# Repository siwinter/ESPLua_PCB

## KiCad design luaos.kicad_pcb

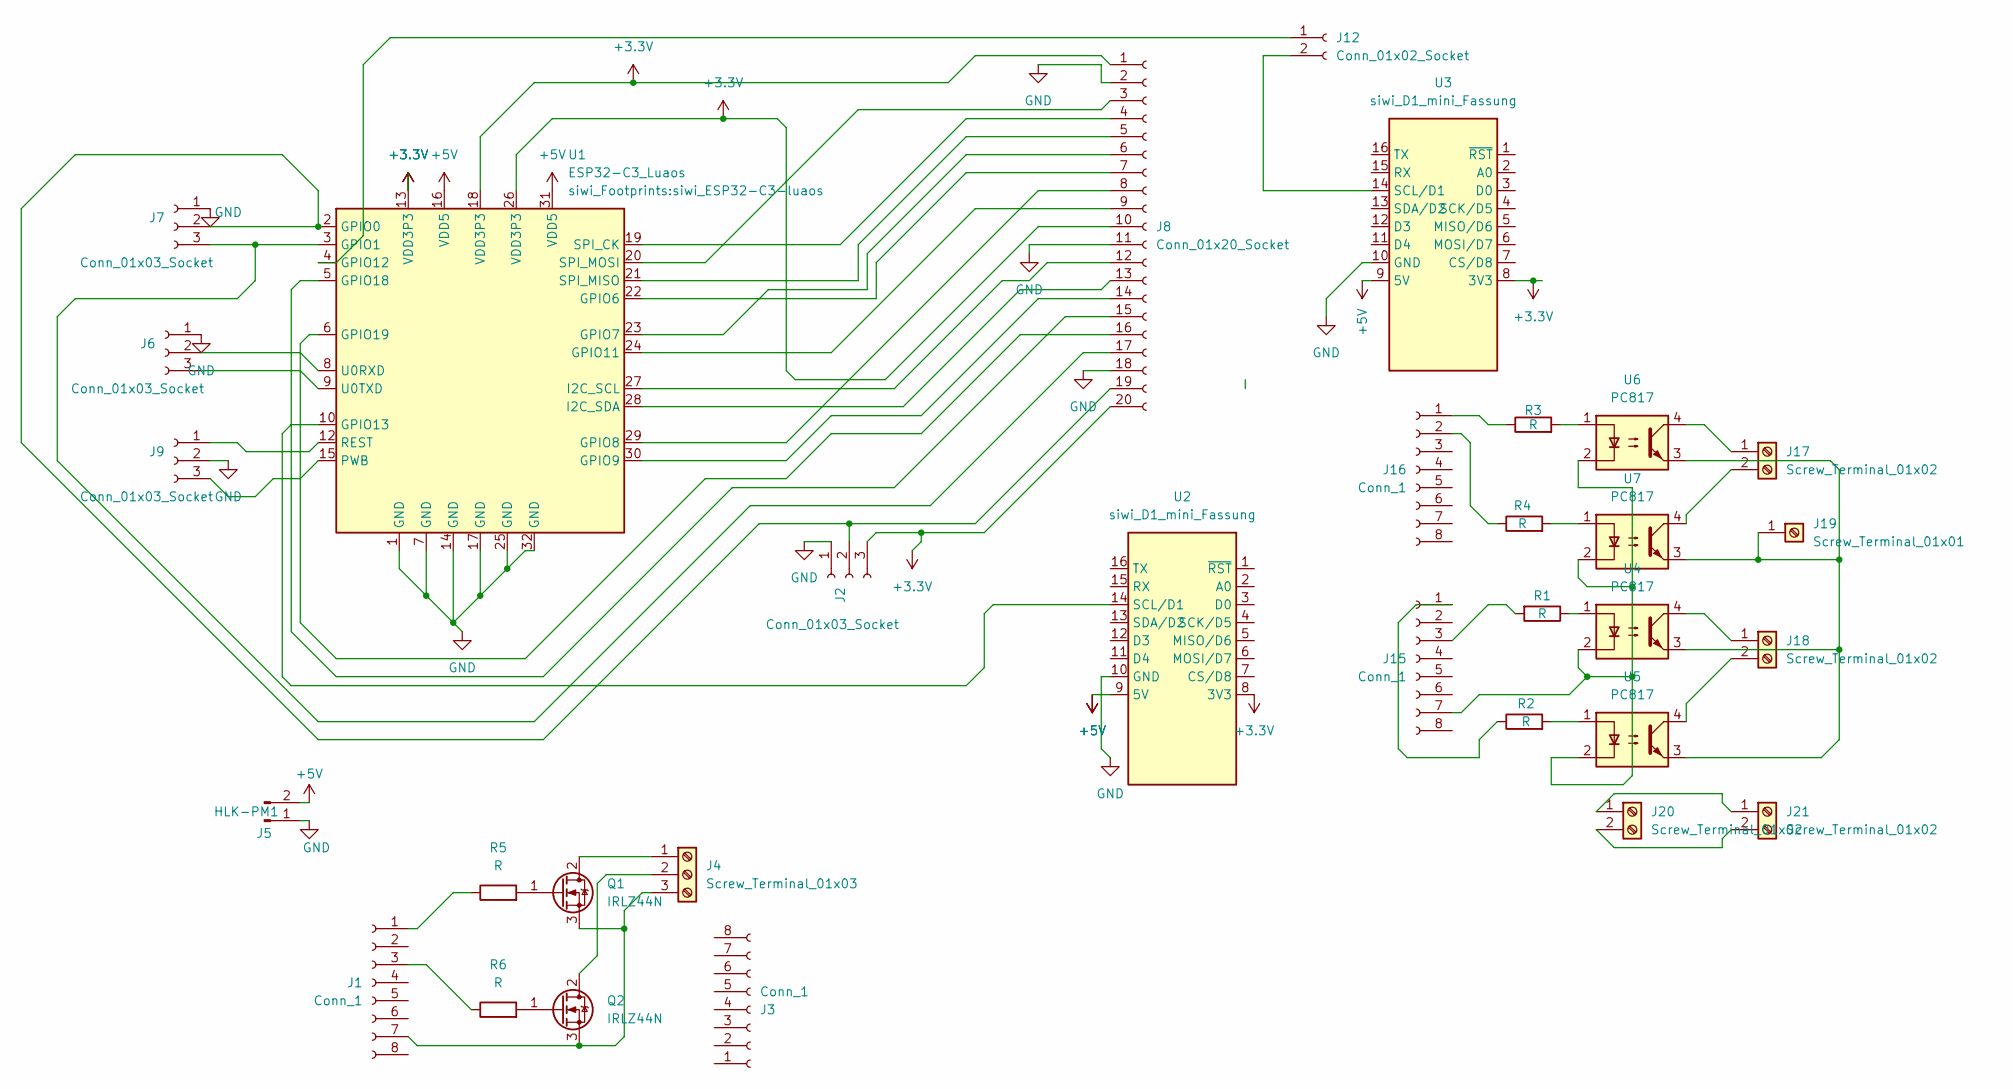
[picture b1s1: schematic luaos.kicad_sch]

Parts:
J1, J3, J15, J16: Conn_1; PinHeader_1x08_P2.54mm_Vertical
J2, J6, J7, J9: Conn_01x03_Socket; PinHeader_1x03_P2.54mm_Vertical
J4: Screw_Terminal_01x03; TerminalBlock_bornier-3_P5.08mm
J5: HLK-PM1; siwi_HLK-PMxx_DC
J8: Conn_01x20_Socket; siwi_PinHeader_2x20_P2.54
J12: Conn_01x02_Socket; PinHeader_1x02_P2.54mm_Vertical
J17, J18, J21: Screw_Terminal_01x02; TerminalBlock_MaiXu_MX126-5.0-02P_1x02_P5.00mm
J19: Screw_Terminal_01x01; TerminalBlock_MetzConnect_360271_1x01_Horizontal_ScrewM3.0_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
J20: Screw_Terminal_01x02; siwi_Converter_ACDC_HLK-5Mxx_230V
Q1, Q2: IRLZ44N; TO-220-3_Vertical
R1, R2, R3, R4, R5, R6: R; siwi_R_Axial_DIN0204_L3.6mm_D1.6mm_P7.62mm_Horizontal
U1: ESP32-C3_Luaos; siwi_ESP32-C3-luaos
U2, U3: siwi_D1_mini_Fassung; siwi_D1_mini_steckplatz
U4, U5, U6, U7: PC817; siwi_PC4SF

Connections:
+3.3V: J2.3, J8.1, J8.10, J8.20, U1.13 (VDD3P3), U1.18 (VDD3P3), U1.26 (VDD3P3), U2.8 (3V3), U3.8 (3V3)
+5V: J5.2, U1.16 (VDD5), U1.31 (VDD5), U2.9 (5V), U3.9 (5V)
GND: J2.1, J5.1, J6.1, J7.1, J8.2, J8.11, J8.18, J9.2, U1.1 (GND), U1.7 (GND), U1.14 (GND), U1.17 (GND), U1.25 (GND), U1.32 (GND), U2.10 (GND), U3.10 (GND)
unnamed: J1.1, R5.1
unnamed: J1.3, R6.1
unnamed: J1.7, J4.3, Q1.3 (S), Q2.3 (S)
unnamed: J2.2, J7.2, J8.19, U1.2 (GPIO0)
unnamed: J4.1, Q1.2 (D)
unnamed: J4.2, Q2.2 (D)
unnamed: J6.2, U1.8 (U0RXD)
unnamed: J6.3, U1.9 (U0TXD)
unnamed: J7.3, J8.17, U1.3 (GPIO1)
unnamed: J8.3, U1.20 (SPI_MOSI)
unnamed: J8.4, U1.19 (SPI_CK)
unnamed: J8.5, U1.21 (SPI_MISO)
unnamed: J8.6, U1.23 (GPIO7)
unnamed: J8.7, U1.22 (GPIO6)
unnamed: J8.8, U1.29 (GPIO8)
unnamed: J8.9, U1.24 (GPIO11)
unnamed: J8.12, U1.27 (I2C_SCL)
unnamed: J8.13, U1.28 (I2C_SDA)
unnamed: J8.14, U1.30 (GPIO9)
unnamed: J8.15, U1.5 (GPIO18)
unnamed: J8.16, U1.6 (GPIO19)
unnamed: J9.1, U1.12 (REST)
unnamed: J9.3, U1.15 (PWB)
unnamed: J12.1, U1.4 (GPIO12)
unnamed: J12.2, U3.14 (SCL/D1)
unnamed: J15.1, R2.1
unnamed: J15.3, R1.2
unnamed: J15.7, U4.2, U5.2, U6.2, U7.2
unnamed: J16.1, R3.1
unnamed: J16.2, R4.1
unnamed: J17.1, U6.4
unnamed: J17.2, U7.4
unnamed: J18.1, U4.4
unnamed: J18.2, U5.4
unnamed: J19.1, U4.3, U5.3, U6.3, U7.3
unnamed: J20.1, J21.1
unnamed: J20.2, J21.2
unnamed: Q1.1 (G), R5.2
unnamed: Q2.1 (G), R6.2
unnamed: R1.1, U4.1
unnamed: R2.2, U5.1
unnamed: R3.2, U6.1
unnamed: R4.2, U7.1
unnamed: U1.10 (GPIO13), U2.14 (SCL/D1)

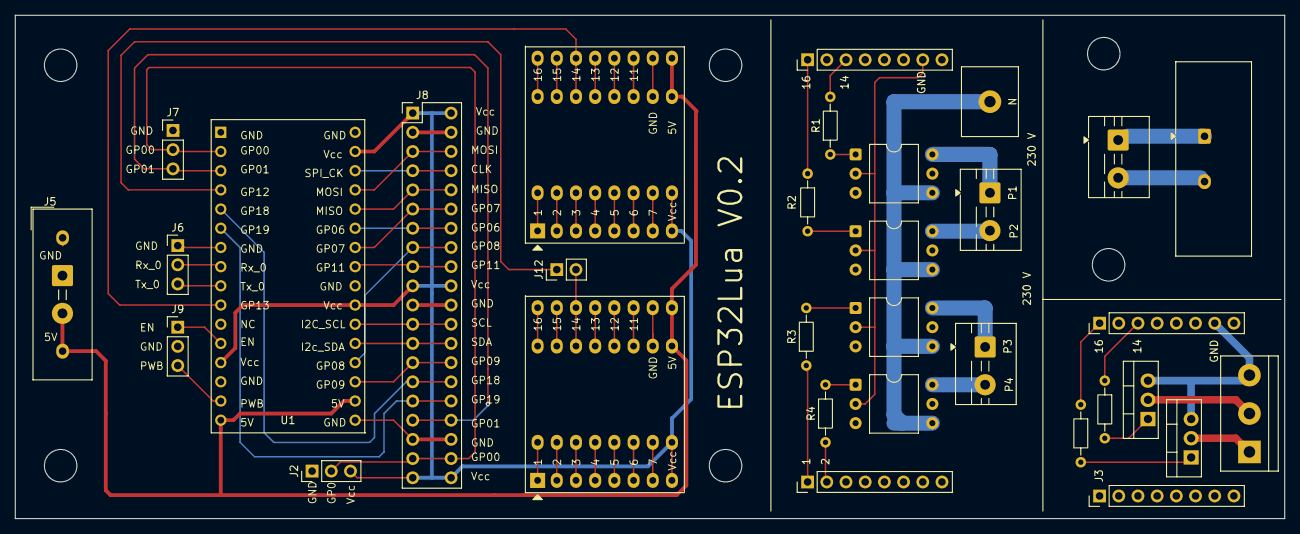
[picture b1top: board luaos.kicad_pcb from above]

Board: 2 copper layers, 168.0 x 66.6 mm, 32 parts (0 on the bottom side), 47 nets.

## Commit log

2025-08-19 Initial commit: KiCad-Projekt angelegt
2025-08-28 Version 0.2 neues PCB Design
